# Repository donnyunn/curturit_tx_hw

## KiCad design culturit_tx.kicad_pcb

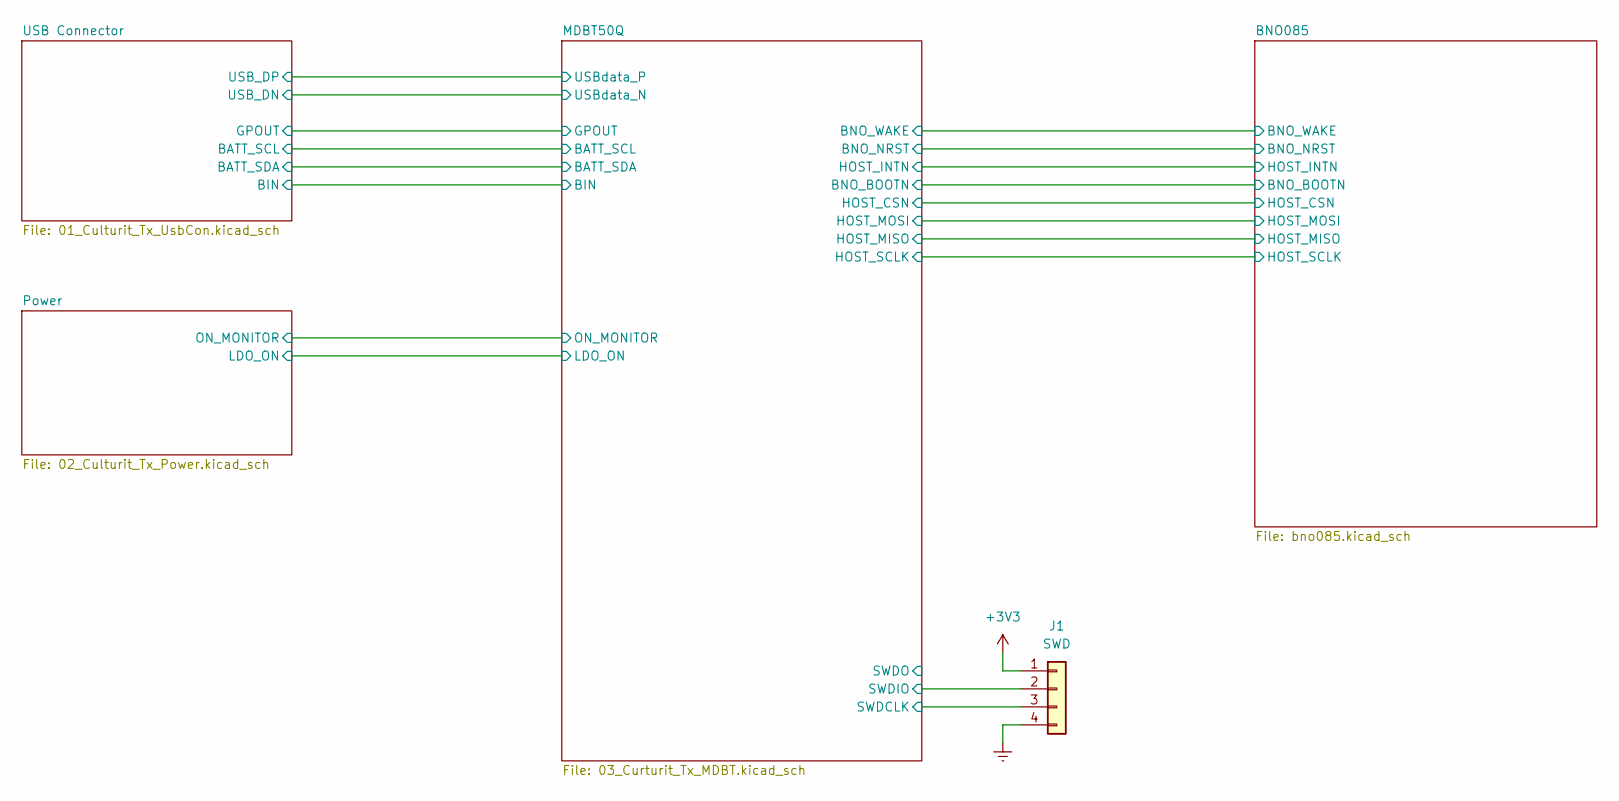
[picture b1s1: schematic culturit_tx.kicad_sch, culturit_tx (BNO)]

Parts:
J1: SWD; PinHeader_1x04_P2.54mm_Vertical

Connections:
+3V3: J1.1; also elsewhere on the board
/MDBT50Q/SWDCLK: J1.3; also elsewhere on the board
/MDBT50Q/SWDIO: J1.2; also elsewhere on the board
Earth: J1.4; also elsewhere on the board

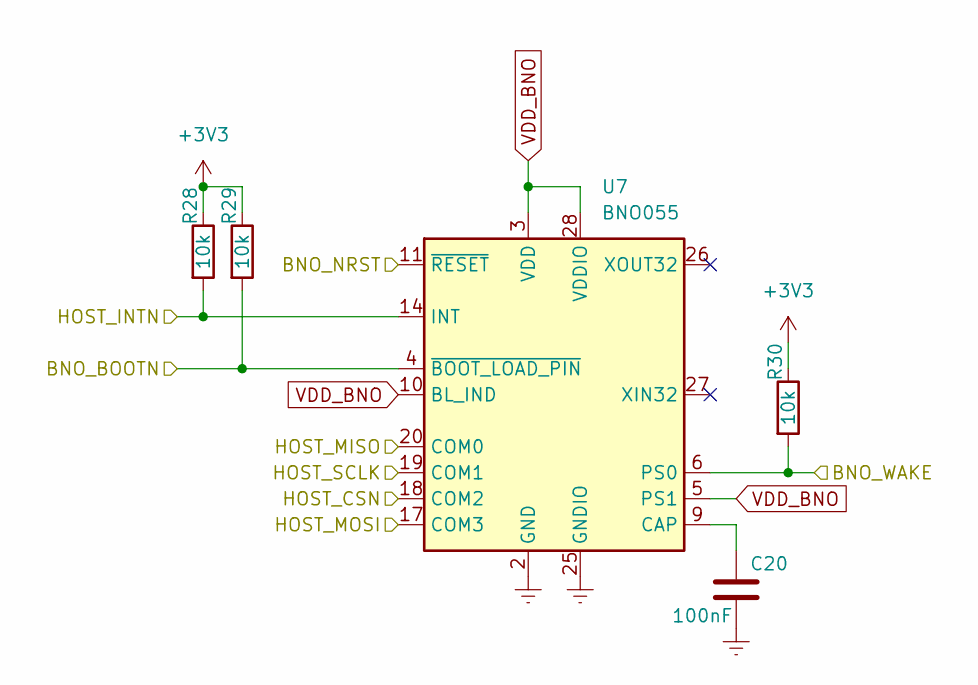
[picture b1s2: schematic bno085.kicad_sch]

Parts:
C20: 100nF; C_0402_1005Metric; MPN CC0402KRX7R7BB104
R28, R29, R30: 10k; R_0402_1005Metric; MPN RC0402FR-0710KL
U7: BNO055; LGA-28_5.2x3.8mm_P0.5mm; MPN BNO085

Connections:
+3V3: R28.1, R29.1, R30.1; also elsewhere on the board
/BNO085/BNO_BOOTN: R29.2, U7.4 (~BOOT_LOAD_PIN); also elsewhere on the board
/BNO085/BNO_NRST: U7.11 (~RESET); also elsewhere on the board
/BNO085/BNO_WAKE: R30.2, U7.6 (PS0); also elsewhere on the board
/BNO085/HOST_CSN: U7.18 (COM2); also elsewhere on the board
/BNO085/HOST_INTN: R28.2, U7.14 (INT); also elsewhere on the board
/BNO085/HOST_MISO: U7.20 (COM0); also elsewhere on the board
/BNO085/HOST_MOSI: U7.17 (COM3); also elsewhere on the board
/BNO085/HOST_SCLK: U7.19 (COM1); also elsewhere on the board
Earth: C20.2, U7.2 (GND), U7.15 (GNDIO), U7.16 (GNDIO), U7.25 (GNDIO); also elsewhere on the board
unnamed: C20.1, U7.9 (CAP)
VDD_BNO: U7.3 (VDD), U7.5 (PS1), U7.10 (BL_IND), U7.28 (VDDIO); also elsewhere on the board

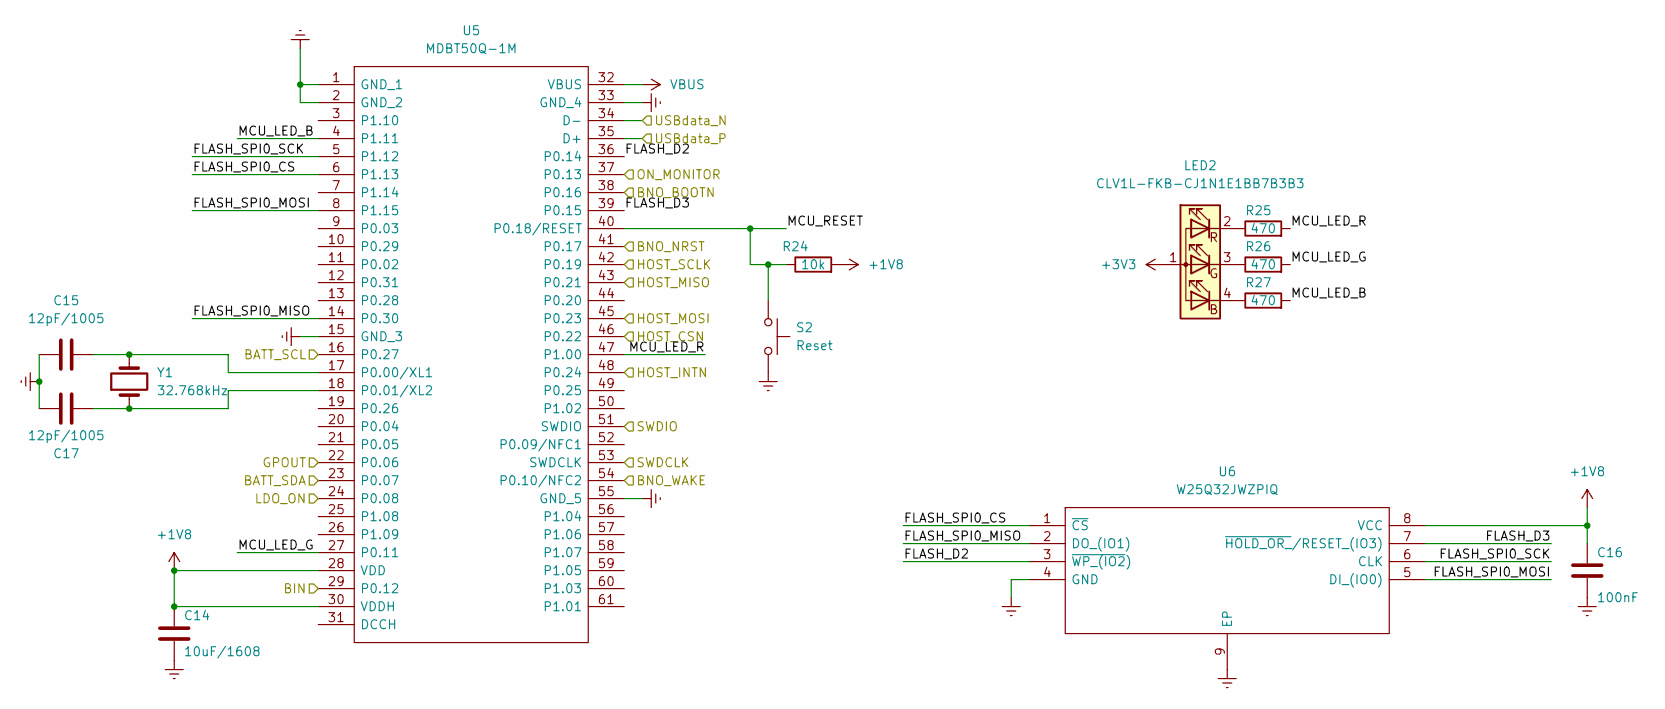
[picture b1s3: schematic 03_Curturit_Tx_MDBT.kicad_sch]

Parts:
C14: 10uF/1608; C_0603_1608Metric; MPN CC0603KRX5R6BB106
C15, C17: 12pF/1005; C_0402_1005Metric
C16: 100nF; C_0402_1005Metric; MPN CC0402KRX7R7BB104
LED2: CLV1L-FKB-CJ1N1E1BB7B3B3; LED_Cree-PLCC4_3.2x2.8mm_CCW; MPN CLV1L-FKB-CJ1N1E1BB7B3B3
R24: 10k; R_0402_1005Metric; MPN RC0402JR-0710KL
R25, R26, R27: 470; R_0402_1005Metric; MPN 0402WGF4700TCE
S2: Reset; SW_SPST_B3U-1000P
U5: MDBT50Q-1M; Mouser Part Number 713-113990583
U6: W25Q32JWZPIQ; SON127P600X500X80-9N-D; Mouser Part Number 454-W25Q32JWZPIQ
Y1: 32.768kHz; Crystal_SMD_2012-2Pin_2.0x1.2mm; MPN FC-12M

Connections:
+1V8: C14.1, C16.1, R24.2, U5.28 (VDD), U5.30 (VDDH), U6.8 (VCC); also elsewhere on the board
+3V3: LED2.1 (A); also elsewhere on the board
/BNO085/BNO_BOOTN: U5.38 (P0.16); also elsewhere on the board
/BNO085/BNO_NRST: U5.41 (P0.17); also elsewhere on the board
/BNO085/BNO_WAKE: U5.54 (P0.10/NFC2); also elsewhere on the board
/BNO085/HOST_CSN: U5.46 (P0.22); also elsewhere on the board
/BNO085/HOST_INTN: U5.48 (P0.24); also elsewhere on the board
/BNO085/HOST_MISO: U5.43 (P0.21); also elsewhere on the board
/BNO085/HOST_MOSI: U5.45 (P0.23); also elsewhere on the board
/BNO085/HOST_SCLK: U5.42 (P0.19); also elsewhere on the board
/MDBT50Q/BATT_SCL: U5.16 (P0.27); also elsewhere on the board
/MDBT50Q/BATT_SDA: U5.23 (P0.07); also elsewhere on the board
/MDBT50Q/BIN: U5.29 (P0.12); also elsewhere on the board
/MDBT50Q/FLASH_D2: U5.36 (P0.14), U6.3 (~WP_(IO2))
/MDBT50Q/FLASH_D3: U5.39 (P0.15), U6.7 (~HOLD_OR_/RESET_(IO3))
/MDBT50Q/FLASH_SPI0_CS: U5.6 (P1.13), U6.1 (~CS)
/MDBT50Q/FLASH_SPI0_MISO: U5.14 (P0.30), U6.2 (DO_(IO1))
/MDBT50Q/FLASH_SPI0_MOSI: U5.8 (P1.15), U6.5 (DI_(IO0))
/MDBT50Q/FLASH_SPI0_SCK: U5.5 (P1.12), U6.6 (CLK)
/MDBT50Q/GPOUT: U5.22 (P0.06); also elsewhere on the board
/MDBT50Q/LDO_ON: U5.24 (P0.08); also elsewhere on the board
/MDBT50Q/MCU_LED_B: R27.2, U5.4 (P1.11)
/MDBT50Q/MCU_LED_G: R26.2, U5.27 (P0.11)
/MDBT50Q/MCU_LED_R: R25.2, U5.47 (P1.00)
/MDBT50Q/MCU_RESET: R24.1, S2.1, U5.40 (P0.18/RESET)
/MDBT50Q/ON_MONITOR: U5.37 (P0.13); also elsewhere on the board
/MDBT50Q/SWDCLK: U5.53 (SWDCLK); also elsewhere on the board
/MDBT50Q/SWDIO: U5.51 (SWDIO); also elsewhere on the board
/MDBT50Q/USBdata_N: U5.34 (D-); also elsewhere on the board
/MDBT50Q/USBdata_P: U5.35 (D+); also elsewhere on the board
Earth: C14.2, C15.1, C16.2, C17.2, S2.2, U5.1 (GND_1), U5.2 (GND_2), U5.15 (GND_3), U5.33 (GND_4), U5.55 (GND_5), U6.4 (GND), U6.9 (EP); also elsewhere on the board
unnamed: C15.2, U5.17 (P0.00/XL1), Y1.2
unnamed: C17.1, U5.18 (P0.01/XL2), Y1.1
unnamed: LED2.2 (RK), R25.1
unnamed: LED2.3 (GK), R26.1
unnamed: LED2.4 (BK), R27.1
VBUS: U5.32 (VBUS); also elsewhere on the board

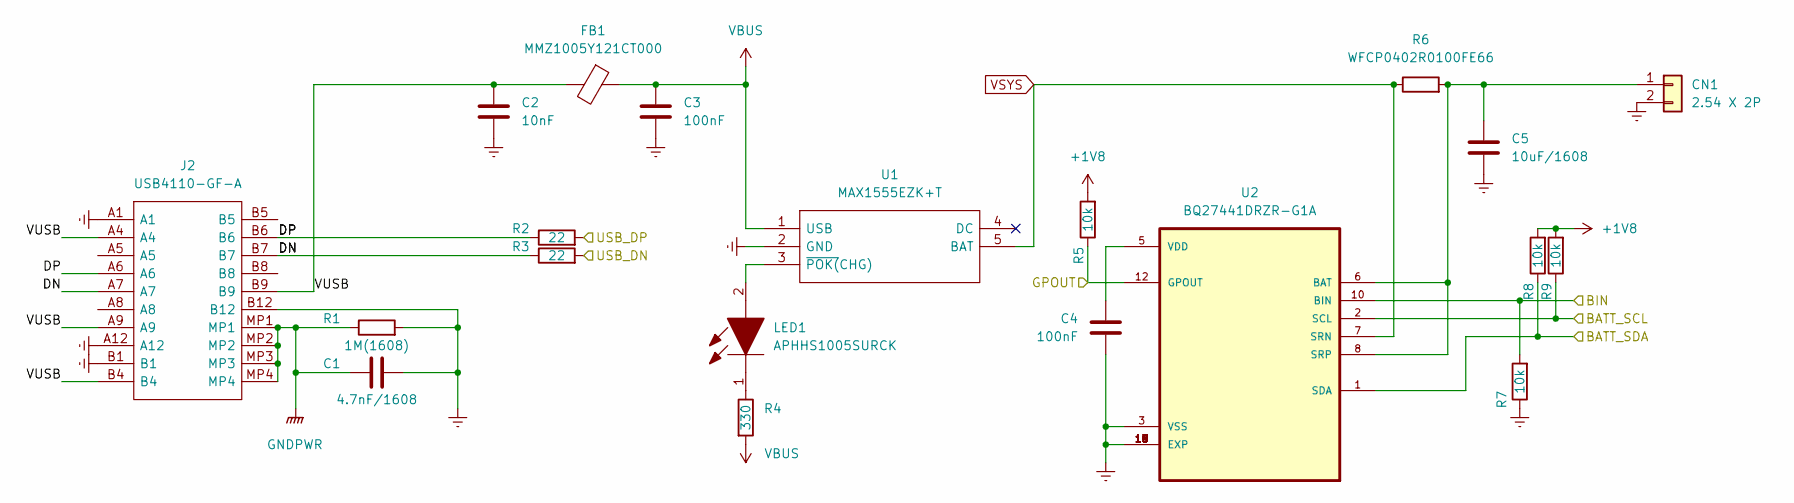
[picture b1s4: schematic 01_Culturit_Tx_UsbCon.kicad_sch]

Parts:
C1: 4.7nF/1608; C_0603_1608Metric; MPN CC0603KRX7R9BB472
C2: 10nF; C_0402_1005Metric; MPN CC0402KRX7R9BB103
C3, C4: 100nF; C_0402_1005Metric; MPN CC0402KRX7R7BB104
C5: 10uF/1608; C_0603_1608Metric; MPN CC0603KRX5R6BB106
CN1: 2.54 X 2P; PinHeader_1x02_P2.54mm_Vertical
FB1: MMZ1005Y121CT000; L_0402_1005Metric; MPN MMZ1005Y121CT000
J2: USB4110-GF-A; USB4110GFA; MPN USB4110-GF-A
LED1: APHHS1005SURCK; LED_0402_1005Metric; Mouser Part Number 604-APHHS1005SURCK
R1: 1M(1608); R_0603_1608Metric; MPN RC0603FR-071ML
R2, R3: 22; R_0402_1005Metric; MPN RC0402FR-0722RL
R4: 330; R_0402_1005Metric; MPN RC0402FR-07330RL
R5, R7, R8, R9: 10k; R_0402_1005Metric; MPN RC0402JR-0710KL
R6: WFCP0402R0100FE66; R_0402_1005Metric; MPN WFCP0402R0100FE66
U1: MAX1555EZK+T; SOT95P275X110-5N; Mouser Part Number 700-MAX1555EZK+T
U2: BQ27441DRZR-G1A; IC_BQ27441DRZR-G1A; MPN BQ27441DRZR-G1A

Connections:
+1V8: R5.2, R8.2, R9.2; also elsewhere on the board
/MDBT50Q/BATT_SCL: R9.1, U2.2 (SCL); also elsewhere on the board
/MDBT50Q/BATT_SDA: R8.1, U2.1 (SDA); also elsewhere on the board
/MDBT50Q/BIN: R7.2, U2.10 (BIN); also elsewhere on the board
/MDBT50Q/GPOUT: R5.1, U2.12 (GPOUT); also elsewhere on the board
/MDBT50Q/USBdata_N: R3.2; also elsewhere on the board
/MDBT50Q/USBdata_P: R2.2; also elsewhere on the board
/USB Connector/DN: J2.A7, J2.B7, R3.1
/USB Connector/DP: J2.A6, J2.B6, R2.1
/USB Connector/VUSB: C2.1, FB1.2, J2.A4, J2.A9, J2.B4, J2.B9
Earth: C1.2, C2.2, C3.2, C4.1, C5.2, CN1.2, J2.A1, J2.A12, J2.B1, J2.B12, R1.2, R7.1, U1.2 (GND), U2.3 (VSS), U2.13 (EXP), U2.14 (EXP), U2.15 (EXP), U2.16 (EXP), U2.17 (EXP), U2.18 (EXP), U2.19 (EXP); also elsewhere on the board
GNDPWR: C1.1, J2.MP1, J2.MP2, J2.MP3, J2.MP4, R1.1
unnamed: C4.2, U2.5 (VDD)
unnamed: C5.1, CN1.1, R6.2, U2.6 (BAT), U2.8 (SRP)
unnamed: LED1.1, R4.1
unnamed: LED1.2, U1.3 (~POK(CHG))
VBUS: C3.1, FB1.1, R4.2, U1.1 (USB); also elsewhere on the board
VSYS: R6.1, U1.5 (BAT), U2.7 (SRN); also elsewhere on the board

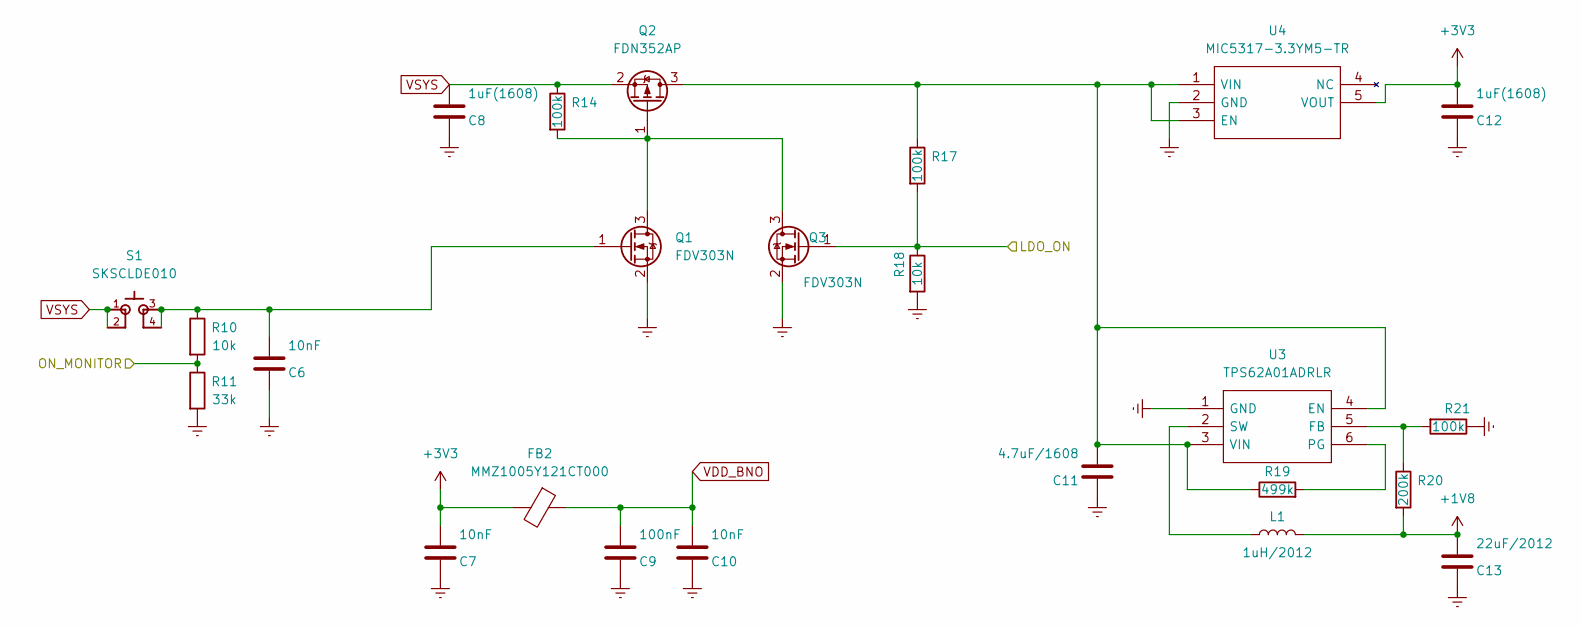
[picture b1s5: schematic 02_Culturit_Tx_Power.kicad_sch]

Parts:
C6, C7, C10: 10nF; C_0402_1005Metric; MPN CC0402KRX7R9BB103
C8, C12: 1uF(1608); C_0603_1608Metric; MPN CC0603KRX7R8BB105
C9: 100nF; C_0402_1005Metric; MPN CC0402KRX7R7BB104
C11: 4.7uF/1608; C_0603_1608Metric; MPN CC0603KRX5R6BB475
C13: 22uF/2012; C_0805_2012Metric; MPN CC0805MKX5R5BB226
FB2: MMZ1005Y121CT000; L_0402_1005Metric; MPN MMZ1005Y121CT000
L1: 1uH/2012; L_0805_2012Metric; MPN LQM21PN1R0MGHL
Q1, Q3: FDV303N; SOT-23; MPN FDV303N
Q2: FDN352AP; SOT-23; MPN FDN352AP
R10: 10k; R_0402_1005Metric; MPN RC0402JR-07910KR
R11: 33k; R_0402_1005Metric; MPN RC0402FR-0733KL
R14, R17, R21: 100k; R_0402_1005Metric; MPN RC0402FR-07100KL
R18: 10k; R_0402_1005Metric; MPN RC0402FR-0710KL
R19: 499k; R_0402_1005Metric; MPN RC0402FR-07499KL
R20: 200k; R_0402_1005Metric; MPN RC0402FR-07200KL
S1: SKSCLDE010; MPN SKSCLDE010
U3: TPS62A01ADRLR; SOTFL50P160X60-6N; Mouser Part Number 595-TPS62A01ADRLR
U4: MIC5317-3.3YM5-TR; SOT95P280X145-5N; MPN MIC5317-3.3YM5-TR

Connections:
+1V8: C13.1, L1.2, R20.2; also elsewhere on the board
+3V3: C7.1, C12.1, FB2.2, U4.5 (VOUT); also elsewhere on the board
/MDBT50Q/LDO_ON: Q3.1 (G), R17.2, R18.1; also elsewhere on the board
/MDBT50Q/ON_MONITOR: R10.2, R11.1; also elsewhere on the board
Earth: C6.2, C7.2, C8.2, C9.2, C10.2, C11.2, C12.2, C13.2, Q1.2 (S), Q3.2 (S), R11.2, R18.2, R21.1, U3.1 (GND), U4.2 (GND); also elsewhere on the board
unnamed: C6.1, Q1.1 (G), R10.1, S1.3, S1.4
unnamed: C11.1, Q2.3 (D), R17.1, R19.1, U3.3 (VIN), U3.4 (EN), U4.1 (VIN), U4.3 (EN)
unnamed: L1.1, U3.2 (SW)
unnamed: Q1.3 (D), Q2.1 (G), Q3.3 (D), R14.2
unnamed: R19.2, U3.6 (PG)
unnamed: R20.1, R21.2, U3.5 (FB)
VDD_BNO: C9.1, C10.1, FB2.1; also elsewhere on the board
VSYS: C8.1, Q2.2 (S), R14.1, S1.1, S1.2; also elsewhere on the board

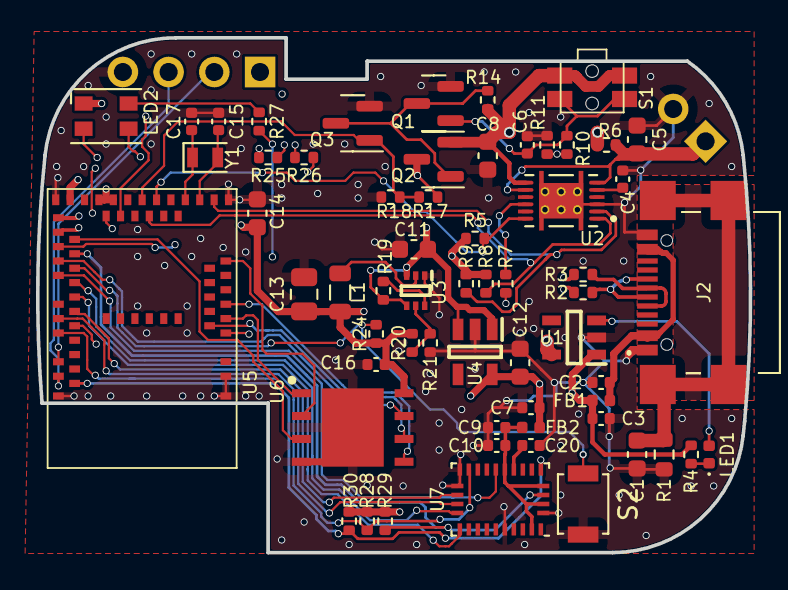
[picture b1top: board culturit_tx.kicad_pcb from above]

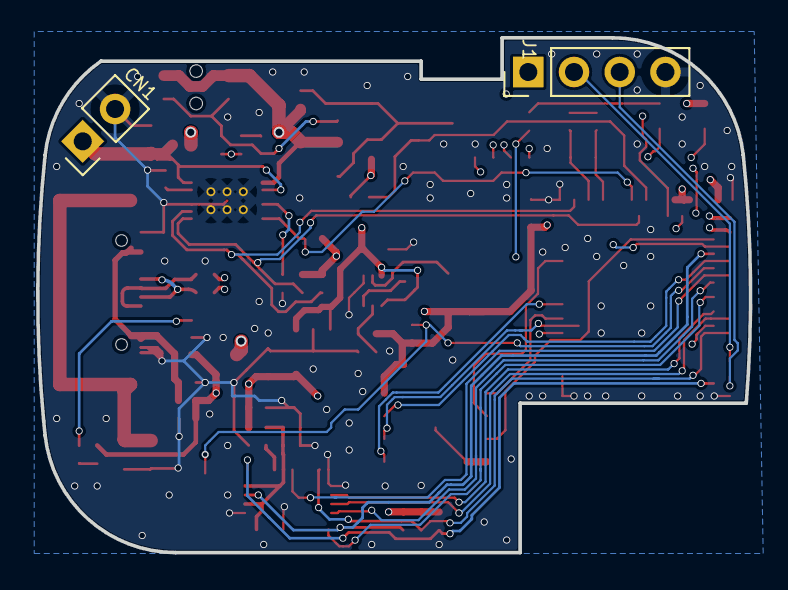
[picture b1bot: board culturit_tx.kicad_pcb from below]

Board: 4 copper layers, 39.6 x 28.6 mm, 63 parts (2 on the bottom side), 54 nets.

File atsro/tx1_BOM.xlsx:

Source: | Culturit_Tx_1
Date: | 44865
Tool: | Eeschema (6.0.0)
Generator: | Jeong Dong-Yun
Component Count: | 62
Collated Components:
Item | Qty | Reference(s) | Value | MPN | Note
1 | 1 | C1 | 4.7nF/1608
2 | 4 | C2, C6, C7, C10 | 10nF/1005
3 | 5 | C3, C4, C9, C16, C20 | 100nF/1005
4 | 1 | C5, C14 | 10uF/1608
5 | 2 | C8, C12 | 1uF/1608
6 | 1 | C11 | 4.7uF/1608
7 | 1 | C13 | 22uF/2012
8 | 2 | C15, C17 | 12pF/1005
9 | 1 | CN1 |  | N.C.
10 | 2 | FB1, FB2 | MMZ1005Y121CT000 | MMZ1005Y121CT000 | https://www.mouser.kr/ProductDetail/TDK/MMZ1005Y121CT000?qs=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
11 | 1 | J1 | SWD | N.C.
12 | 1 | J2 | USB4110-GF-A | USB4110-GF-A | https://www.mouser.kr/ProductDetail/GCT/USB4110-GF-A?qs=KUoI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
13 | 1 | L1 | 1uH/2012 | LQM21PN1R0MGHL | https://www.mouser.kr/ProductDetail/Murata-Electronics/LQM21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
14 | 1 | LED1 | APHHS1005SURCK | APHHS1005SURCK | https://www.mouser.kr/ProductDetail/Kingbright/APHHS1005SURC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
15 | 1 | LED2 | CLV1L-FKB-CJ1N1E1BB7B3B3 | CLV1L-FKB-CJ1N1E1BB7B3B3 | https://www.mouser.kr/ProductDetail/Cree-LED/CLV1L-FKB-CJ1N1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
16 | 2 | Q1, Q3 | FDV303N | FDV303N | https://www.mouser.kr/ProductDetail/onsemi-Fairchild/FDV303N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
17 | 1 | Q2 | FDN352AP | FDN352AP | https://www.mouser.kr/ProductDetail/onsemi-Fairchild/FDN352A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
18 | 1 | R1 | 1M/1608
19 | 2 | R2, R3 | 22/1005
20 | 1 | R4 | 330/1005
21 | 10 | R5, R7, R8, R9, R10, R18, R24, R28, R29, R30 | 10k/1005
22 | 1 | R6 | 10mΩ/1005 | WFCP0402R0100FE66 | https://www.mouser.kr/ProductDetail/Vishay/WFCP0402R0100FE66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
23 | 1 | R11 | 33k/1005
24 | 3 | R14, R17, R21 | 100k/1005
25 | 1 | R19 | 499k/1005
26 | 1 | R20 | 200k/1005
27 | 3 | R25, R26, R27 | 470/1005
28 | 1 | S1 | SKSCLDE010 | SKSCLDE010 | https://www.mouser.kr/ProductDetail/Alps-Alpine/SKSCLDE010?q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
29 | 1 | S2 |  | N.C.
30 | 1 | U1 | MAX1555EZK+T | MAX1555EZK+T | https://www.mouser.kr/ProductDetail/Maxim-Integrated/MAX1555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
31 | 1 | U2 | BQ27441DRZR-G1A | BQ27441DRZR-G1A | https://www.mouser.kr/ProductDetail/Texas-Instruments/BQ2744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
32 | 1 | U3 | TPS62A01ADRLR | TPS62A01ADRLR | https://www.mouser.kr/ProductDetail/Texas-Instruments/TPS62A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
33 | 1 | U4 | MIC5317-3.3YM5-TR | MIC5317-3.3YM5-TR | https://www.mouser.kr/ProductDetail/Microchip-Technology-Atm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
34 | 1 | U5 | MDBT50Q-1M | MDBT50Q-M1V2
35 | 1 | U6 | W25Q32JWZPIQ | W25Q32JWZPIQ | https://www.mouser.kr/ProductDetail/Winbond/W25Q32JWZPIQ?qs=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
36 | 1 | U7 | BNO085 | BNO085 | 사급 가능 (15개 보유)
37 | 1 | Y1 | 32.768kHz/2012 | FC-12M 32.7680KA-A5 | https://www.mouser.kr/ProductDetail/Epson-Timing/FC-12M-32.7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

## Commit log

2022-08-05 2022-08-05
2022-08-08 2022-08-08
2022-08-09 2022-08-09
2022-08-10 2022-08-10
2022-08-10 2022-08-11
2022-08-11 2022-08-11 2
2022-08-16 2022-08-16
2022-08-24 2022-08-24
2022-08-25 2022-08-25
2022-08-26 2022-08-26
2022-08-29 2022-08-29
2022-09-05 2022-09-05
2022-09-05 bno085 branch
2022-09-06 2022-09-06 1
2022-09-07 2022-09-07
2022-09-07 2022-09-07 2
2022-09-07 2022-09-07 3
2022-09-14 2022-09-14
2022-09-14 2022-09-14 2
2022-10-05 2022-10-05
2022-10-12 gitignore modified
2022-10-13 2022-10-13
2022-10-14 2022-10-14
2022-10-24 2022-10-24 added crystal
2022-10-27 2022-10-27
2022-10-30 2022-10-30
2022-10-31 2022-11-01
2022-10-31 2022-11-01 2
2022-11-15 20221115
2022-11-15 2022-11-15
2022-11-23 2022-11-23
2022-11-24 2022-11-24
